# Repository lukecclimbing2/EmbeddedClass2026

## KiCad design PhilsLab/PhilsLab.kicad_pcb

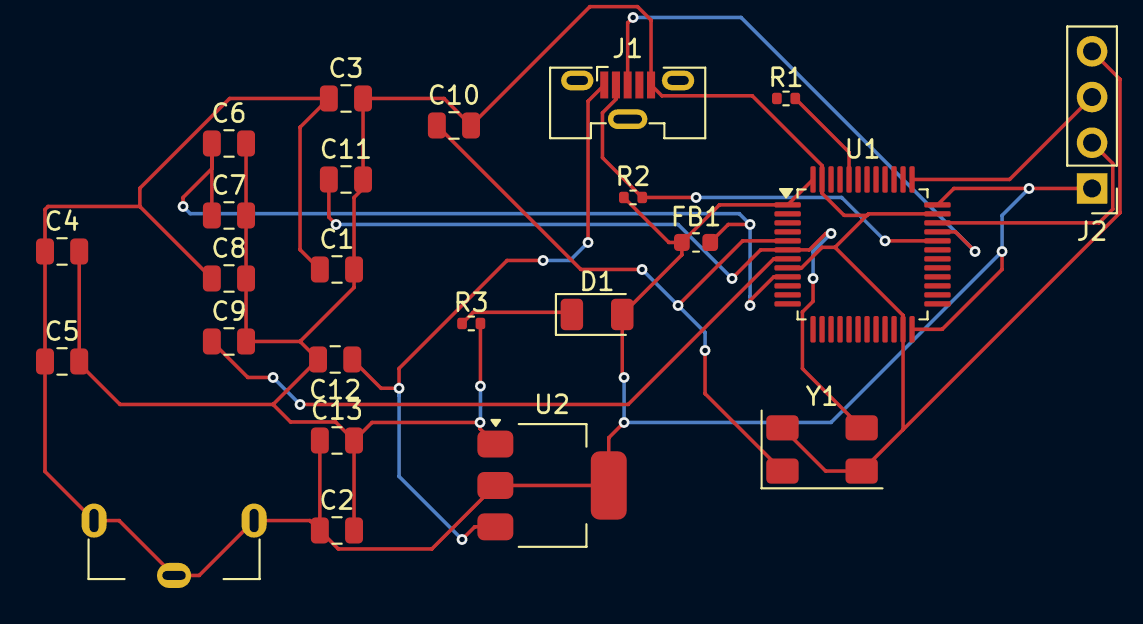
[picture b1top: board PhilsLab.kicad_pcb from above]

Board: 2 copper layers, 24 parts (0 on the bottom side), 13 nets.

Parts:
C1, C2, C3, C4, C9: 100n; C_0805_2012Metric
C5: 10u; C_0805_2012Metric
C6: 10n; C_0805_2012Metric
C7, C8: 1u; C_0805_2012Metric
C10, C11: 10p; C_0805_2012Metric
C12, C13: 22u; C_0805_2012Metric
D1: LED; LED_1206_3216Metric
FB1: 120R; L_0603_1608Metric
J1: USB_B_Micro; USB_Micro-B_Molex-105133-0031
J2: Conn_01x04_Pin; PinHeader_1x04_P2.54mm_Vertical
R1: 10k; R_0402_1005Metric
R2: 1k5; R_0402_1005Metric
R3: 1K5; R_0402_1005Metric
SW1: SW_SPDT; BatteryHolder_Keystone_590
U1: STM32F103C8Tx; LQFP-48_7x7mm_P0.5mm
U2: AMS1117; SOT-223-3_TabPin2
Y1: Crystal_GND24; Crystal_SMD_0603-4Pin_6.0x3.5mm

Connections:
+3.3V: C1.1, C2.1, C3.1, C4.1, C5.1, C8.1, C13.1, D1.2 (A), FB1.1, J2.1, R2.1, SW1.1 (A), U1.1 (VBAT), U1.24 (VDD), U1.36 (VDD), U1.48 (VDD), U2.2 (VO)
+3.3VA: C6.1, C7.1, FB1.2, U1.9 (VDDA)
GND: C1.2, C2.2, C3.2, C4.2, C5.2, C6.2, C7.2, C8.2, C9.2, C10.2, C11.2, C12.2, C13.2, J1.5 (GND), J2.4, R3.2, U1.8 (VSSA), U1.23 (VSS), U1.35 (VSS), U1.47 (VSS), U2.1 (ADJ), Y1.2 (G), Y1.4 (G)
unnamed: D1.1 (K), R3.1
unnamed: J1.3 (D+), U1.33 (PA12)
unnamed: J1.2 (D-), R2.2, U1.32 (PA11)
unnamed: J2.2, U1.34 (PA13)
unnamed: J2.3, U1.37 (PA14)
unnamed: R1.2, U1.44 (BOOT0)
unnamed: C9.1, U1.7 (NRST)
unnamed: C10.1, U1.5 (PD0), Y1.1
unnamed: C11.1, U1.6 (PD1), Y1.3
VBUS: C12.1, J1.1 (VBUS), U2.3 (VI)
